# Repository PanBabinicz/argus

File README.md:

# Argus

> **Argus** is a tiny keylogger built around the [CH32V003](https://www.wch-ic.com/products/CH32V003.html),
> a low-cost 32-bit RISC-V microcontroller. It captures keystrokes and discreetly
> stores or forwards them, all from a minimal footprint built on bare-metal firmware
> and a custom PCB.

> [!NOTE]
> **Please bear in mind that the workspace was primarily created for enjoyment
> and educational endeavors.**

> The MIT License (MIT)
>
> Copyright (c) 2011-2024 The Bootstrap Authors
>
> Permission is hereby granted, free of charge, to any person obtaining a copy
> of this software and associated documentation files (the "Software"), to deal
> in the Software without restriction, including without limitation the rights
> to use, copy, modify, merge, publish, distribute, sublicense, and/or sell
> copies of the Software, and to permit persons to whom the Software is
> furnished to do so, subject to the following conditions:
>
> The above copyright notice and this permission notice shall be included in
> all copies or substantial portions of the Software.
>
> THE SOFTWARE IS PROVIDED "AS IS", WITHOUT WARRANTY OF ANY KIND, EXPRESS OR
> IMPLIED, INCLUDING BUT NOT LIMITED TO THE WARRANTIES OF MERCHANTABILITY,
> FITNESS FOR A PARTICULAR PURPOSE AND NONINFRINGEMENT. IN NO EVENT SHALL THE
> AUTHORS OR COPYRIGHT HOLDERS BE LIABLE FOR ANY CLAIM, DAMAGES OR OTHER
> LIABILITY, WHETHER IN AN ACTION OF CONTRACT, TORT OR OTHERWISE, ARISING FROM,
> OUT OF OR IN CONNECTION WITH THE SOFTWARE OR THE USE OR OTHER DEALINGS IN
> THE SOFTWARE.

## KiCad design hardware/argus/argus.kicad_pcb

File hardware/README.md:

# Argus Hardware

> [!NOTE]
> **Please bear in mind that the pcb was primarily created for enjoyment
> and educational endeavors.**

> This is the first version of the board, featuring only basic functionality.

## 🛠️  PCB

> This section showcases the 3D views of the PCB, generated using KiCad.
> These models provide a clear visual reference for component placement,
> board layout, and connector orientation.

### KiCAD 3D Model

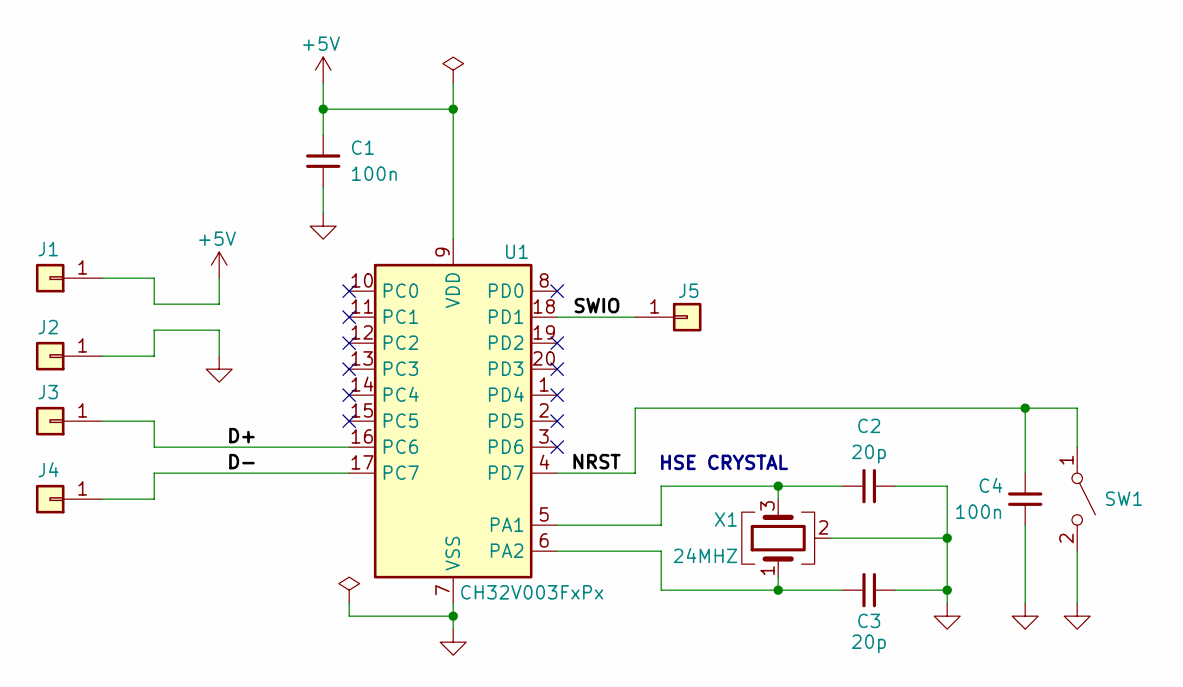
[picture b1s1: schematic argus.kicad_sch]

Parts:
C1, C4: 100n; C_0603_1608Metric
C2, C3: 20p; C_0603_1608Metric
J1, J2, J3, J4, J5: Conn_01x01; Pin_D0.7mm_L6.5mm_W1.8mm_FlatFork
SW1: SW_SPST; SW_SPST_EVQPE1
U1: CH32V003FxPx; TSSOP-20_4.4x6.5mm_P0.65mm
X1: 24MHZ; Crystal_SMD_2520-4Pin_2.5x2.0mm

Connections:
+5V: C1.1, J1.1 (Pin_1_1), U1.9 (VDD)
/D+: J3.1 (Pin_1_1), U1.16 (PC6)
/D-: J4.1 (Pin_1_1), U1.17 (PC7)
/NRST: C4.1, SW1.1 (A), U1.4 (PD7)
/SWIO: J5.1 (Pin_1_1), U1.18 (PD1)
GND: C1.2, C2.2, C3.2, C4.2, J2.1 (Pin_1_1), SW1.2 (B), U1.7 (VSS), X1.2 (G), X1.4 (G)
unnamed: C2.1, U1.5 (PA1), X1.3
unnamed: C3.1, U1.6 (PA2), X1.1

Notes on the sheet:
HSE CRYSTAL

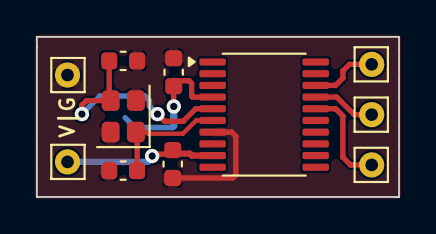
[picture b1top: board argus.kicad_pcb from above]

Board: 2 copper layers, 20.1 x 8.9 mm, 12 parts (1 on the bottom side), 8 nets.
